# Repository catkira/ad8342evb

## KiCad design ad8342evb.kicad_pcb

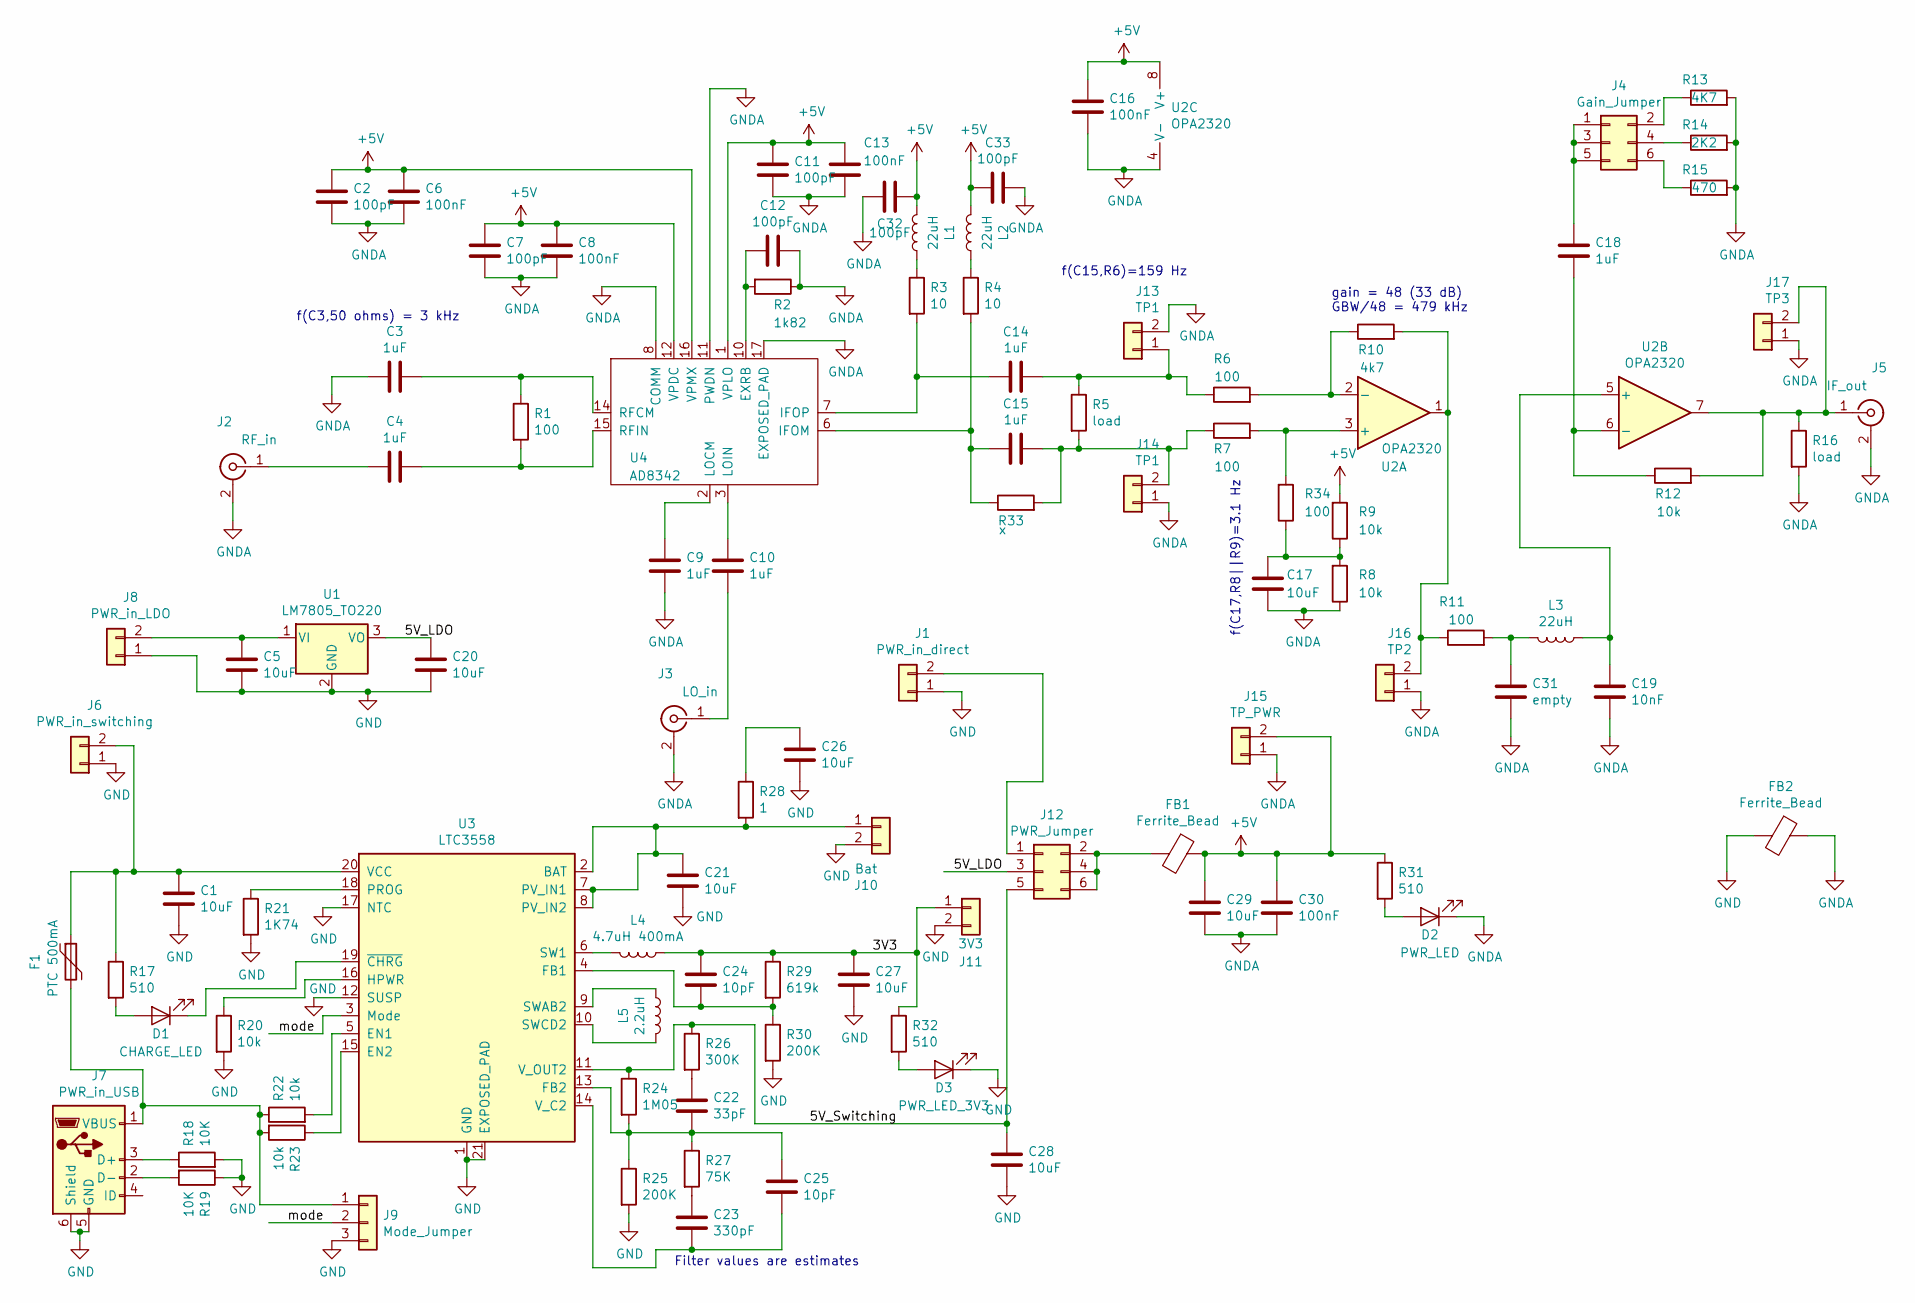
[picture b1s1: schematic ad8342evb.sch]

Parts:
C1, C5, C17, C20, C21, C26, C27, C28, C29: 10uF; C_0805_2012Metric_Pad1.15x1.40mm_HandSolder
C2, C7, C11, C12, C32, C33: 100pF; C_0805_2012Metric_Pad1.15x1.40mm_HandSolder
C3, C4, C9, C10, C14, C15, C18: 1uF; C_0805_2012Metric_Pad1.15x1.40mm_HandSolder
C6, C8, C13, C16, C30: 100nF; C_0805_2012Metric_Pad1.15x1.40mm_HandSolder
C19: 10nF; C_0805_2012Metric_Pad1.15x1.40mm_HandSolder
C22: 33pF; C_0805_2012Metric_Pad1.15x1.40mm_HandSolder
C23: 330pF; C_0805_2012Metric_Pad1.15x1.40mm_HandSolder
C24, C25: 10pF; C_0805_2012Metric_Pad1.15x1.40mm_HandSolder
C31: empty; C_0805_2012Metric_Pad1.15x1.40mm_HandSolder
D1: CHARGE_LED; LED_0805_2012Metric_Pad1.15x1.40mm_HandSolder
D2: PWR_LED; LED_0805_2012Metric_Pad1.15x1.40mm_HandSolder
D3: PWR_LED_3V3; LED_0805_2012Metric_Pad1.15x1.40mm_HandSolder
F1: PTC 500mA; Fuse_1812_4532Metric_Pad1.30x3.40mm_HandSolder
FB1, FB2: Ferrite_Bead; L_0805_2012Metric_Pad1.15x1.40mm_HandSolder
J1: PWR_in_direct; PinHeader_1x02_P2.54mm_Vertical
J2: RF_in; SMA_Amphenol_132134_Vertical
J3: LO_in; SMA_Amphenol_132134_Vertical
J4: Gain_Jumper; PinHeader_2x03_P2.54mm_Vertical
J5: IF_out; SMA_Amphenol_132134_Vertical
J6: PWR_in_switching; PinHeader_1x02_P2.54mm_Vertical
J7: PWR_in_USB; USB_Micro-B_Molex-105017-0001
J8: PWR_in_LDO; PinHeader_1x02_P2.54mm_Vertical
J9: Mode_Jumper; PinHeader_1x03_P2.54mm_Vertical
J10: Bat; PinHeader_1x02_P2.54mm_Vertical
J11: 3V3; PinHeader_1x02_P2.54mm_Vertical
J12: PWR_Jumper; PinHeader_2x03_P2.54mm_Vertical
J13, J14: TP1; TestPoint_2Pads_Pitch2.54mm_Drill0.8mm
J15: TP_PWR; TestPoint_2Pads_Pitch2.54mm_Drill0.8mm
J16: TP2; TestPoint_2Pads_Pitch2.54mm_Drill0.8mm
J17: TP3; TestPoint_2Pads_Pitch2.54mm_Drill0.8mm
L1, L2, L3: 22uH; L_1008_2520Metric
L4: 4.7uH 400mA; L_1008_2520Metric
L5: 2.2uH; L_1008_2520Metric
R1, R6, R7, R11, R34: 100; R_0805_2012Metric_Pad1.15x1.40mm_HandSolder
R2: 1k82; R_0805_2012Metric_Pad1.15x1.40mm_HandSolder
R3, R4: 10; R_0805_2012Metric_Pad1.15x1.40mm_HandSolder
R5, R16: load; R_0805_2012Metric_Pad1.15x1.40mm_HandSolder
R8, R9, R12, R20, R22, R23: 10k; R_0805_2012Metric_Pad1.15x1.40mm_HandSolder
R10: 4k7; R_0805_2012Metric_Pad1.15x1.40mm_HandSolder
R13: 4K7; R_0805_2012Metric_Pad1.15x1.40mm_HandSolder
R14: 2K2; R_0805_2012Metric_Pad1.15x1.40mm_HandSolder
R15: 470; R_0805_2012Metric_Pad1.15x1.40mm_HandSolder
R17, R31, R32: 510; R_0805_2012Metric_Pad1.15x1.40mm_HandSolder
R18, R19: 10K; R_0805_2012Metric_Pad1.15x1.40mm_HandSolder
R21: 1K74; R_0805_2012Metric_Pad1.15x1.40mm_HandSolder
R24: 1M05; R_0805_2012Metric_Pad1.15x1.40mm_HandSolder
R25, R30: 200K; R_0805_2012Metric_Pad1.15x1.40mm_HandSolder
R26: 300K; R_0805_2012Metric_Pad1.15x1.40mm_HandSolder
R27: 75K; R_0805_2012Metric_Pad1.15x1.40mm_HandSolder
R28: 1; R_0805_2012Metric_Pad1.15x1.40mm_HandSolder
R29: 619k; R_0805_2012Metric_Pad1.15x1.40mm_HandSolder
R33: x; R_0805_2012Metric_Pad1.15x1.40mm_HandSolder
U1: LM7805_TO220; TO-220-3_Vertical
U2: OPA2320; SOIC-8_3.9x4.9mm_P1.27mm
U3: LTC3558; QFN-20-1EP_3x3mm_P0.4mm_EP1.65x1.65mm
U4: AD8342; LFCSP-16-1EP_3x3mm_P0.5mm_EP1.6x1.6mm

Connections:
+5V: C2.1, C6.1, C7.1, C8.1, C11.1, C13.1, C16.1, C29.1, C30.1, C32.2, C33.1, FB1.1, J15.2, L1.2, L2.2, R9.2, R31.1, U2.8 (V+), U4.1 (VPLO), U4.12 (VPDC), U4.16 (VPMX)
/3V3: C24.1, C27.1, J11.1, L4.1, R29.1, R32.1
/5V_LDO: C20.1, J12.3, U1.3 (VO)
/5V_Switching: C28.1, J12.5, R24.1, R26.1, U3.11 (V_OUT2)
/mode: J9.2, U3.3 (Mode)
GND: C1.2, C5.2, C20.2, C21.2, C26.2, C27.2, C28.2, D3.1 (K), FB2.2, J1.1, J6.1, J7.5 (GND), J7.6 (Shield), J8.1, J9.3, J10.2, J11.2, R18.2, R19.1, R20.2, R21.2, R25.2, R30.2, U1.2 (GND), U3.1 (GND), U3.12 (SUSP), U3.17 (NTC), U3.21 (EXPOSED_PAD)
GNDA: C2.2, C3.2, C6.2, C7.2, C8.2, C9.2, C11.2, C12.1, C13.2, C16.2, C17.1, C19.2, C29.2, C30.2, C31.2, C32.1, C33.2, D2.1 (K), FB2.1, J2.2 (Ext), J3.2 (Ext), J5.2 (Ext), J13.2, J14.1, J15.1, J16.1, J17.1, R2.1, R8.1, R13.2, R14.2, R15.2, R16.2, U2.4 (V-), U4.4 (COMM), U4.5 (COMM), U4.8 (COMM), U4.9 (COMM), U4.11 (PWDN), U4.13 (COMM), U4.17 (EXPOSED_PAD)
unnamed: C1.1, F1.1, J6.2, R17.1, U3.20 (VCC)
unnamed: C3.1, R1.1, U4.14 (RFCM)
unnamed: C4.1, R1.2, U4.15 (RFIN)
unnamed: C4.2, J2.1 (In)
unnamed: C5.1, J8.2, U1.1 (VI)
unnamed: C9.1, U4.2 (LOCM)
unnamed: C10.1, U4.3 (LOIN)
unnamed: C10.2, J3.1 (In)
unnamed: C12.2, R2.2, U4.10 (EXRB)
unnamed: C14.1, R3.2, U4.7 (IFOP)
unnamed: C14.2, J13.1, R5.1, R6.1
unnamed: C15.1, R4.2, R33.1, U4.6 (IFOM)
unnamed: C15.2, J14.2, R5.2, R7.1, R33.2
unnamed: C17.2, R8.2, R9.1, R34.1
unnamed: C18.1, J4.1, J4.3, J4.5
unnamed: C18.2, R12.1, U2.6 (-)
unnamed: C19.1, L3.1, U2.5 (+)
unnamed: C21.1, J10.1, R28.2, U3.2 (BAT), U3.7 (PV_IN1), U3.8 (PV_IN2)
unnamed: C22.1, R26.2
unnamed: C22.2, C25.1, R24.2, R25.1, R27.1, U3.13 (FB2)
unnamed: C23.1, R27.2
unnamed: C23.2, C25.2, U3.14 (V_C2)
unnamed: C24.2, R29.2, R30.1, U3.4 (FB1)
unnamed: C26.1, R28.1
unnamed: C31.1, L3.2, R11.2
unnamed: D1.1 (K), U3.19 (~CHRG~)
unnamed: D1.2 (A), R17.2
unnamed: D2.2 (A), R31.2
unnamed: D3.2 (A), R32.2
unnamed: F1.2, J7.1 (VBUS), J9.1, R22.1, R23.2
unnamed: FB1.2, J12.2, J12.4, J12.6
unnamed: J1.2, J12.1
unnamed: J4.2, R13.1
unnamed: J4.4, R14.1
unnamed: J4.6, R15.1
unnamed: J7.2 (D-), R19.2
unnamed: J7.3 (D+), R18.1
unnamed: J16.2, R10.2, R11.1, U2.1
unnamed: J5.1 (In), J17.2, R12.2, R16.1, U2.7
unnamed: L1.1, R3.1
unnamed: L2.1, R4.1
unnamed: L4.2, U3.6 (SW1)
unnamed: L5.1, U3.9 (SWAB2)
unnamed: L5.2, U3.10 (SWCD2)
unnamed: R6.2, R10.1, U2.2 (-)
unnamed: R20.1, U3.16 (HPWR)
unnamed: R21.1, U3.18 (PROG)
unnamed: R22.2, U3.5 (EN1)
unnamed: R23.1, U3.15 (EN2)
unnamed: R7.2, R34.2, U2.3 (+)

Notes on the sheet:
Filter values are estimates
gain = 48 (33 dB) GBW/48 = 479 kHz
f(C15,R6)=159 Hz
f(C17,R8||R9)=3.1 Hz
f(C3,50 ohms) = 3 kHz

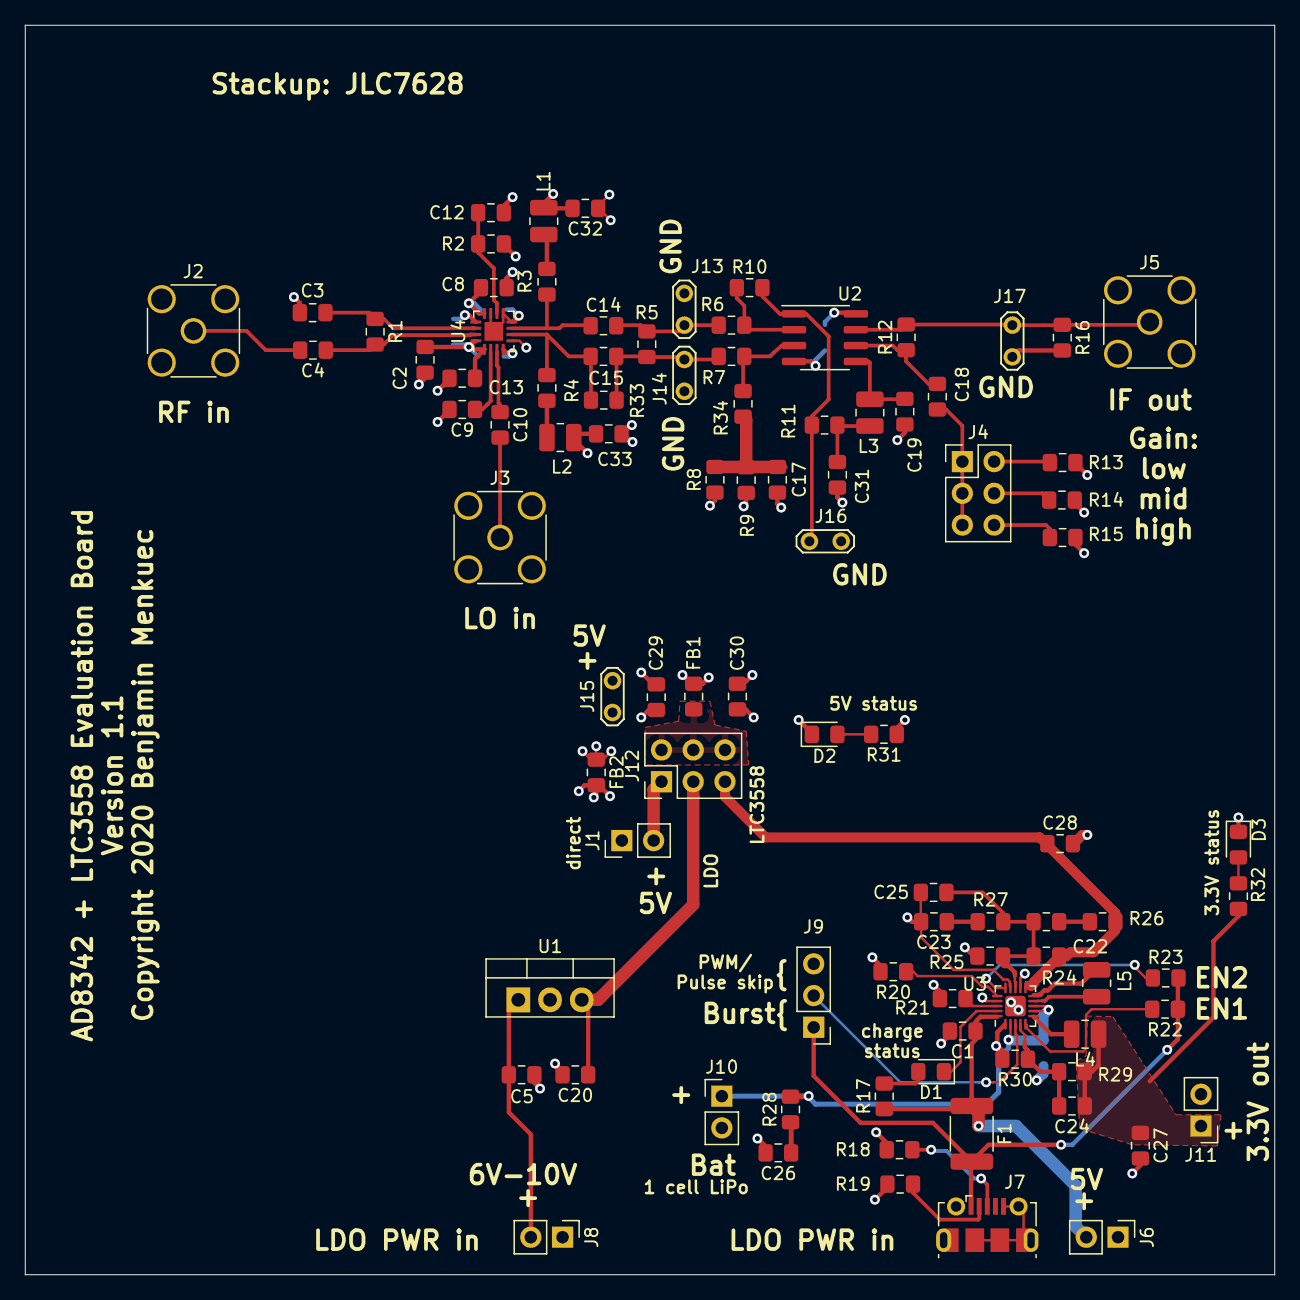
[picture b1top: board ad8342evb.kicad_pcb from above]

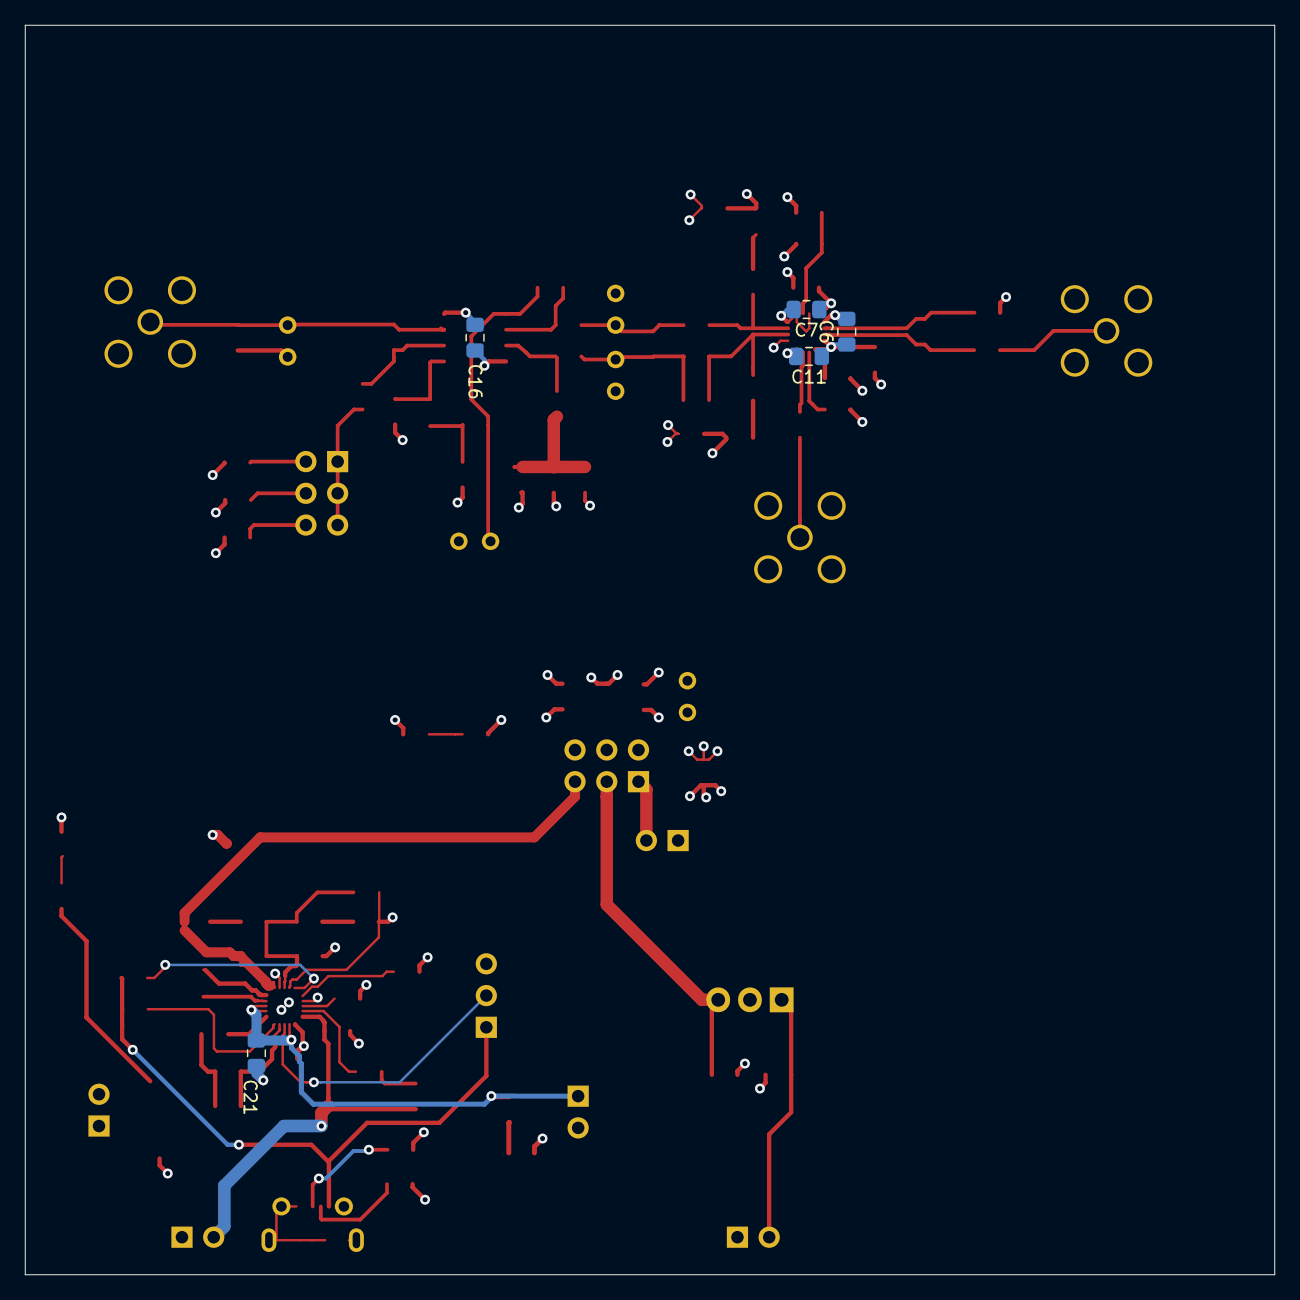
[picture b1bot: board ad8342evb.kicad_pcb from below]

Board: 4 copper layers, 100.0 x 100.0 mm, 99 parts (5 on the bottom side), 57 nets.

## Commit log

2020-07-22 finished schematic
2020-07-22 changed LPF to Pi type
2020-07-23 added different power options
2020-07-23 finished layout
2020-07-24 added separate GNDA plane
2020-08-05 fixed some bugs
2020-08-05 removed v1 from filename
2020-08-06 fixed mistake in schematic
2020-08-06 added DC bias resistor for OPAMP
2020-08-06 moved bias resistor to correct location
2020-08-06 modified bias circuit
2020-08-06 update component values
2020-08-07 added more decoupling caps

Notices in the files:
ad8342evb.kicad_pcb:
Copyright 2020 Benjamin Menkuec
